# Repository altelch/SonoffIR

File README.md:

# SonoffIR
Sonoff IR remote controll extension for [Sonoff-Tasmota](https://github.com/arendst/Sonoff-Tasmota "Sonoff-Tasmota") and [iTead Sonoff Basic](http://sonoff.itead.cc/en/products/sonoff/sonoff-basic).
## Schematics

The resistor values depend on the used IR LED and the gain of the NPN Transistor. Rb is not really necessary an can be left out. R1 limits the current through the diod and can have Values between 2.5 Ohm and 10 Ohm. Using lower values gives you a better range but you risk the diod if the current gets to high. About 100mA are ok for sending signals. Check your datasheets!
## Board layout

The diode is facing upwards, the rest downwards. The board directly fits onto the Sonoff pinheader used for programming and uses GPIO14.
## Assembly
### Parts

### Board prototype

### Parts fitted

### Chassis with additional hole drilled (5mm)

### The finished SonoffIR

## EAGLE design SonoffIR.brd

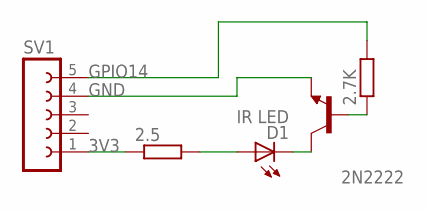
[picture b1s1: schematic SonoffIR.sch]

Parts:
2.5, 2.7K: R-EU_0204/2V; 0204V
2N2222: 2N3565; TO92
D1: IR LED; SFH482
SV1: FE05-1

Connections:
3V3: 2.5.1, SV1.1
GND: 2N2222.3 (E), SV1.4
GPIO14: 2.7K.2, SV1.5
unnamed: 2.5.2, D1.A
unnamed: 2.7K.1, 2N2222.2 (B)
unnamed: 2N2222.1 (C), D1.K (C)

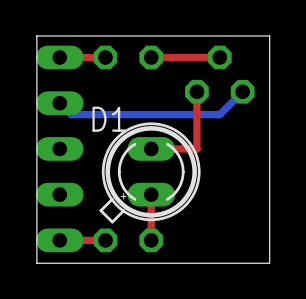
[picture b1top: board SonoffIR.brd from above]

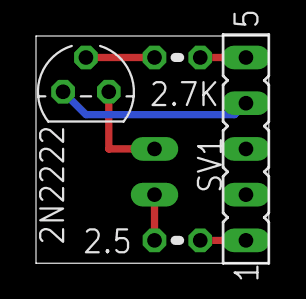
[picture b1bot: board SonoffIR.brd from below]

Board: 2 copper layers, 12.9 x 12.6 mm, 5 parts (4 on the bottom side), 6 nets.

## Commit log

2017-02-13 Sonoff IR remote controller hardware
2017-02-13 Added photos
2017-02-13 Renamed files
2017-02-13 Better Name/Value placement on Board
2017-02-13 Changes in Value placement
